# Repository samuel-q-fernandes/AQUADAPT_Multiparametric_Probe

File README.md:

# Development of a Cost-Effective Multiparametric Probe for Continuous, Real-Time Monitoring of Aquatic Environments

**AQUADAPT | AQUA-V1** is an open-source platform for in-situ water-quality/quantity monitoring (**pH, electrical conductivity (EC), temperature, and water level**). The system targets robust, long-term field deployments with an emphasis on reproducibility, traceability, and low total cost.

The hardware integrates an **ESP32** controller (LILYGO® T-Call with **SIM800L**) for data acquisition and processing, plus **GSM/GPRS** telemetry, **microSD** logging, and **solar power** support (MPPT + Li-ion). Firmware duty-cycles sensing and transmission, then enters **deep sleep** between cycles to minimize average power consumption, enabling multi-day autonomy and continuous operation under normal sunlight.

This repository provides the full stack: **KiCad** design files, **Arduino/C++** firmware, a **PHP API** for authenticated data ingest, the **SQL schema** to bootstrap the database, and a **web dashboard** for data visualization. Documentation includes wiring, configuration, deployment notes, and server setup.

To support transparent metrology, the docs also detail the complete measurement workflow and a **GUM-conforming uncertainty budget** (expanded uncertainties reported at *k* = 2), making results auditable across deployments. A link to the peer-reviewed manuscript will be added here upon acceptance.

Software is released under the **MIT License** (see `LICENSE`). 
**A link to the peer-reviewed manuscript will be added here upon acceptance by the journal.**

## Bill of Materials (BOM)

*A summarized BOM based on the components described in the manuscript. 

> **Target cost:** sub-€1,000 (sensor/probe choices and enclosure options drive most of the variation).

| Subsystem | Item / Model | Qty | Notes |
|---|---|---:|---|
| **MCU, comms & logging** | **LILYGO® TTGO T-Call v1.4** (ESP32 + SIM800L) | 1 | ESP32 controller with integrated GSM/GPRS modem; UART to modem, SPI to microSD. |
|  | **microSD module + 16 GB microSD card** | 1 | On-device redundant logging (CSV/JSON). |
| **Analog / digital interfaces** | **EZO™ Isolator / isolated carrier (pH)** | 1 | Electrical isolation to reduce ground/EMI coupling into pH front-end. |
|  | **EZO™ Conductivity (EC) Circuit** | 1 | Digital EC interface (I²C/UART); temperature aware as configured. |
|  | **MT3608 DC–DC boost converter** | 1 | Boost supply (e.g., 5 V → 12–36 V) for the level/pressure sensor. |
| **Sensors** | **Mini Lab-grade pH probe (ENV-20-pH)** | 1 | Glass electrode; used with Nernst temperature compensation. |
|  | **Mini Conductivity probe K = 1.0 (ENV-20-EC-K1.0)** | 1 | EC probe; three-point calibration via cell constant. |
|  | **DS18B20 temperature sensor** | 1 | 12-bit (0.0625 °C); OneWire; **4.7 kΩ** pull-up to Vcc. |
|  | **Industrial submersible pressure/level sensor (0–5 m)** | 1 | Analog output; hydrostatic level; powered via MT3608 boost. |
| **Custom PCB** | **Main carrier PCB (≈100 × 100 mm)** | 1 | Breakouts and headers for pH/EC/level/DS18B20, modem, power rails, and microSD. |
| **Power** | **PV panel (≈6 V / 5 W)** | 1 | Solar charging for autonomous operation. |
|  | **MPPT charge/power manager (≈900 mA charge)** | 1 | Manages PV → Li-ion charging and system power. |
|  | **Li-ion battery (3.7 V, ~4000 mAh)** | 1 | Energy storage; supports multi-day duty cycle. |
| **Cabling & enclosure** | **IP-rated enclosure with cable glands** | 1 | Houses electronics; strain relief and desiccant recommended. |
|  | **Sensor cable harness (~7 m)** | 2 | Extends probes from housing to water column. |
| **Passives** | **4.7 kΩ resistor** | 1 | DS18B20 pull-up. |
|  | **Sense resistor ~120 Ω (level channel)** | 1 | Per level/pressure readout design. |
| **Calibration materials** | **pH buffers (e.g., pH 4, 7, 9, 10; traceable)** | set | Used for multi-point pH calibration at measurement temperature. |
|  | **EC standards (e.g., 1413, 12 880, 80 000 µS/cm)** | set | Used to estimate cell constant and verify linearity. |

### Sourcing and integration notes
- **Region & connectivity:** confirm 2G/GPRS availability; if unavailable, substitute LTE-M/NB-IoT modem with matching firmware and power profile.  
- **Power budget:** size PV and battery for sampling + telemetry duty cycle and local insolation; include winter/cloud margins.  
- **EMI & grounding:** keep high-impedance pH paths short and away from digital lines; consider shielded cables and star-grounding.  
- **Calibration traceability:** document buffer/standard lot numbers, temperatures, and dates; store calibration IDs in firmware/config.

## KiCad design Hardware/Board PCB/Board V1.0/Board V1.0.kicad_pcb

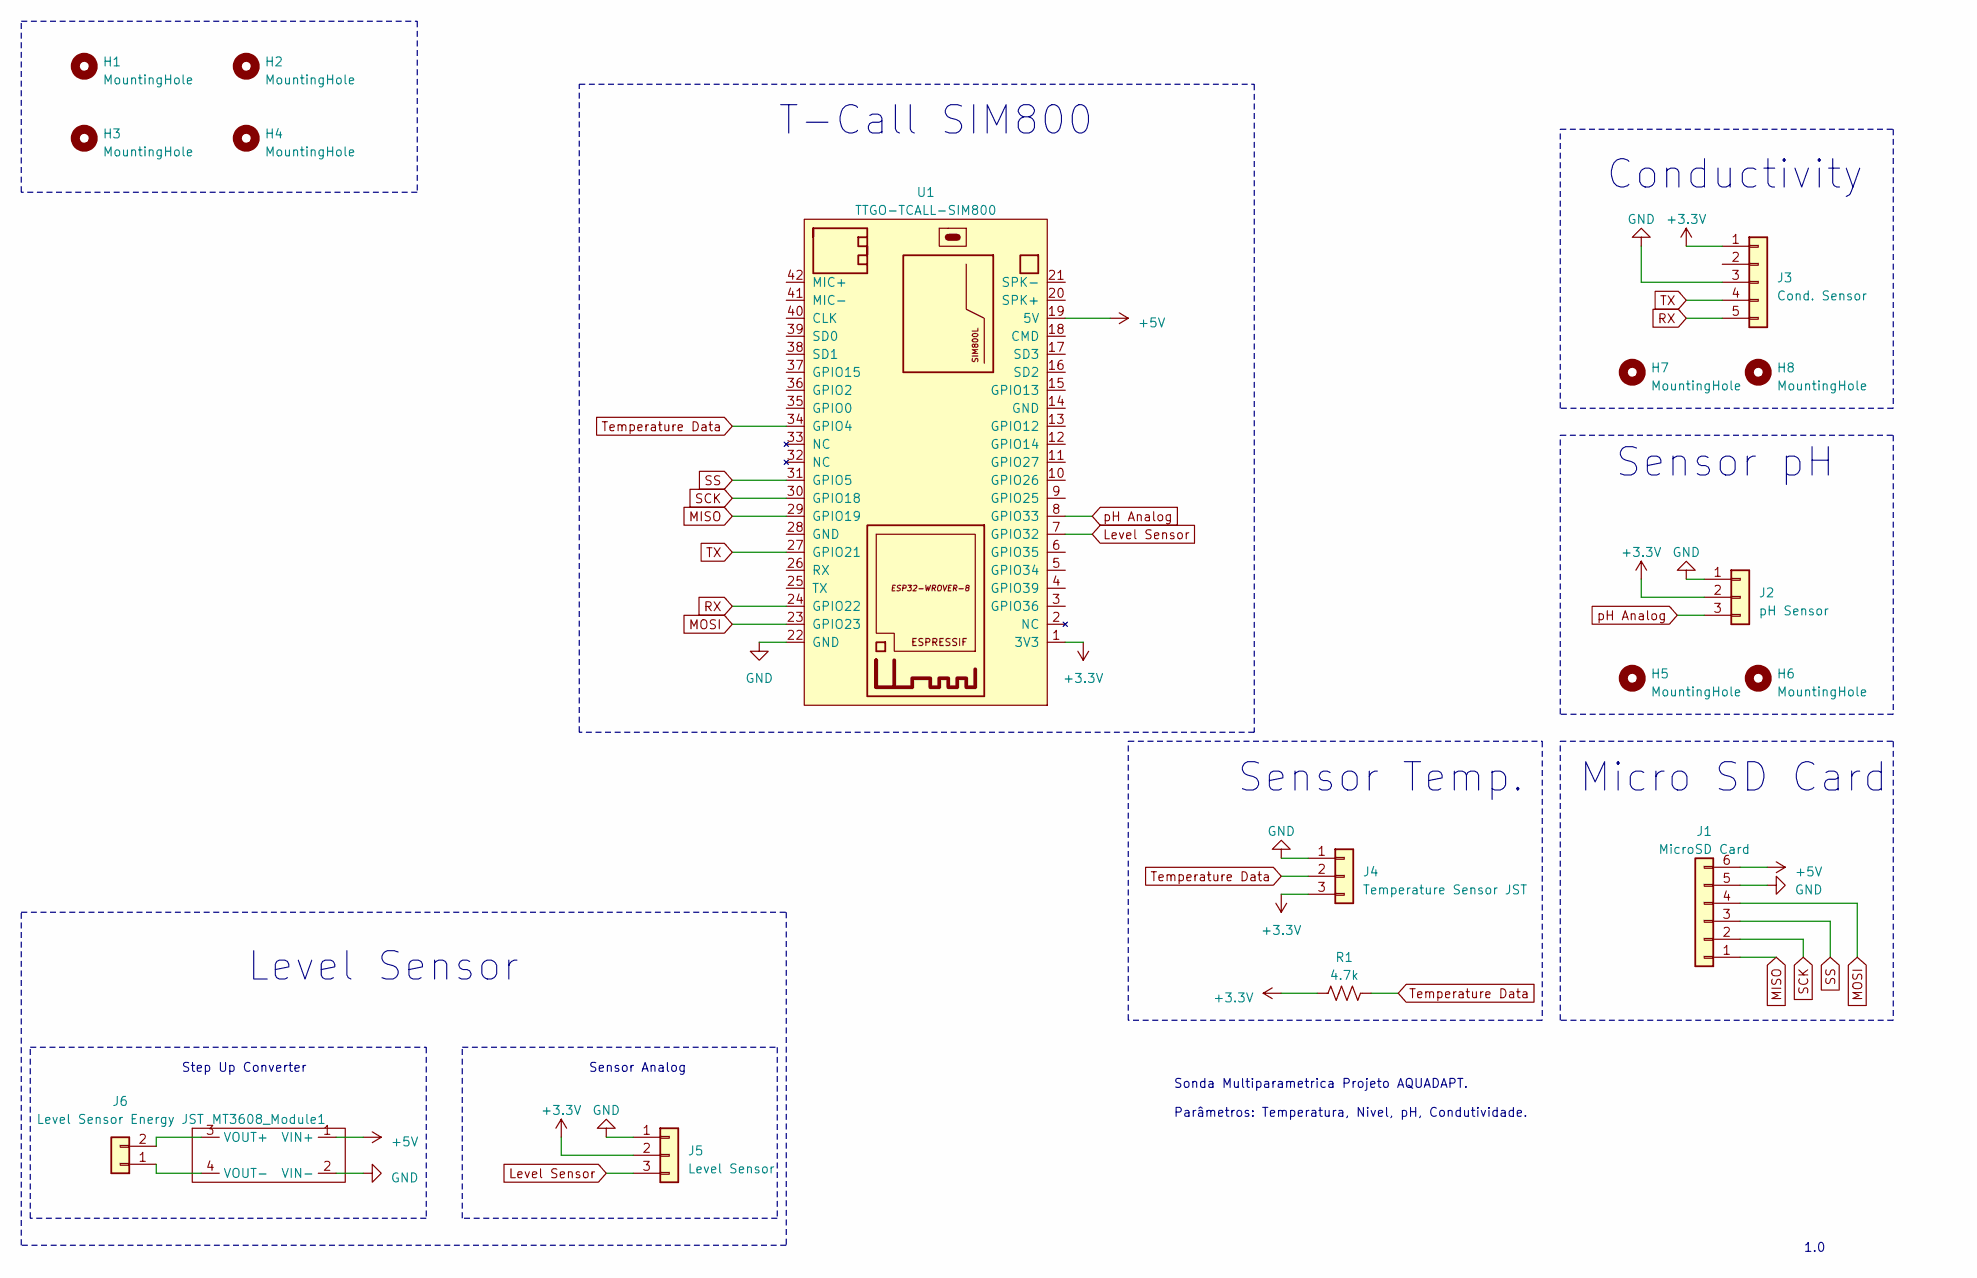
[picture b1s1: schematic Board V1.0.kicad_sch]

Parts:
H1, H2, H3, H4, H5, H6, H7, H8: MountingHole; MountingHole_3mm
J1: MicroSD Card; PinSocket_1x06_P2.54mm_Vertical
J2: pH Sensor; PinSocket_1x03_P2.54mm_Vertical
J3: Cond. Sensor; PinSocket_1x05_P2.54mm_Vertical
J4: Temperature Sensor JST; PinSocket_1x03_P2.54mm_Vertical
J5: Level Sensor; PinSocket_1x03_P2.54mm_Vertical
J6: Level Sensor Energy JST; PinSocket_1x02_P2.54mm_Vertical
MT3608_Module1: MT3608-Module
R1: 4.7k; R_Axial_DIN0207_L6.3mm_D2.5mm_P10.16mm_Horizontal
U1: TTGO-TCALL-SIM800

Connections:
+3.3V: J2.2, J3.1, J4.3, J5.2, R1.1, U1.1 (3V3)
+5V: J1.6, MT3608_Module1.1 (VIN+), U1.19 (5V)
GND: J1.5, J2.1, J3.3, J4.1, J5.1, MT3608_Module1.2 (VIN-), U1.22 (GND)
Level Sensor: J5.3, U1.7 (GPIO32)
MISO: J1.1, U1.29 (GPIO19)
MOSI: J1.4, U1.23 (GPIO23)
unnamed: J6.1, MT3608_Module1.4 (VOUT-)
unnamed: J6.2, MT3608_Module1.3 (VOUT+)
RX: J3.5, U1.24 (GPIO22)
SCK: J1.2, U1.30 (GPIO18)
SS: J1.3, U1.31 (GPIO5)
TX: J3.4, U1.27 (GPIO21)
Temperature Data: J4.2, R1.2, U1.34 (GPIO4)
pH Analog: J2.3, U1.8 (GPIO33)

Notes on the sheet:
Sensor Temp.
Step Up Converter
Conductivity
Sonda Multiparametrica Projeto AQUADAPT. Parâmetros: Temperatura, Nivel, pH, Condutividade.
T-Call SIM800
Sensor Analog
1.0
Sensor pH
Level Sensor
Micro SD Card

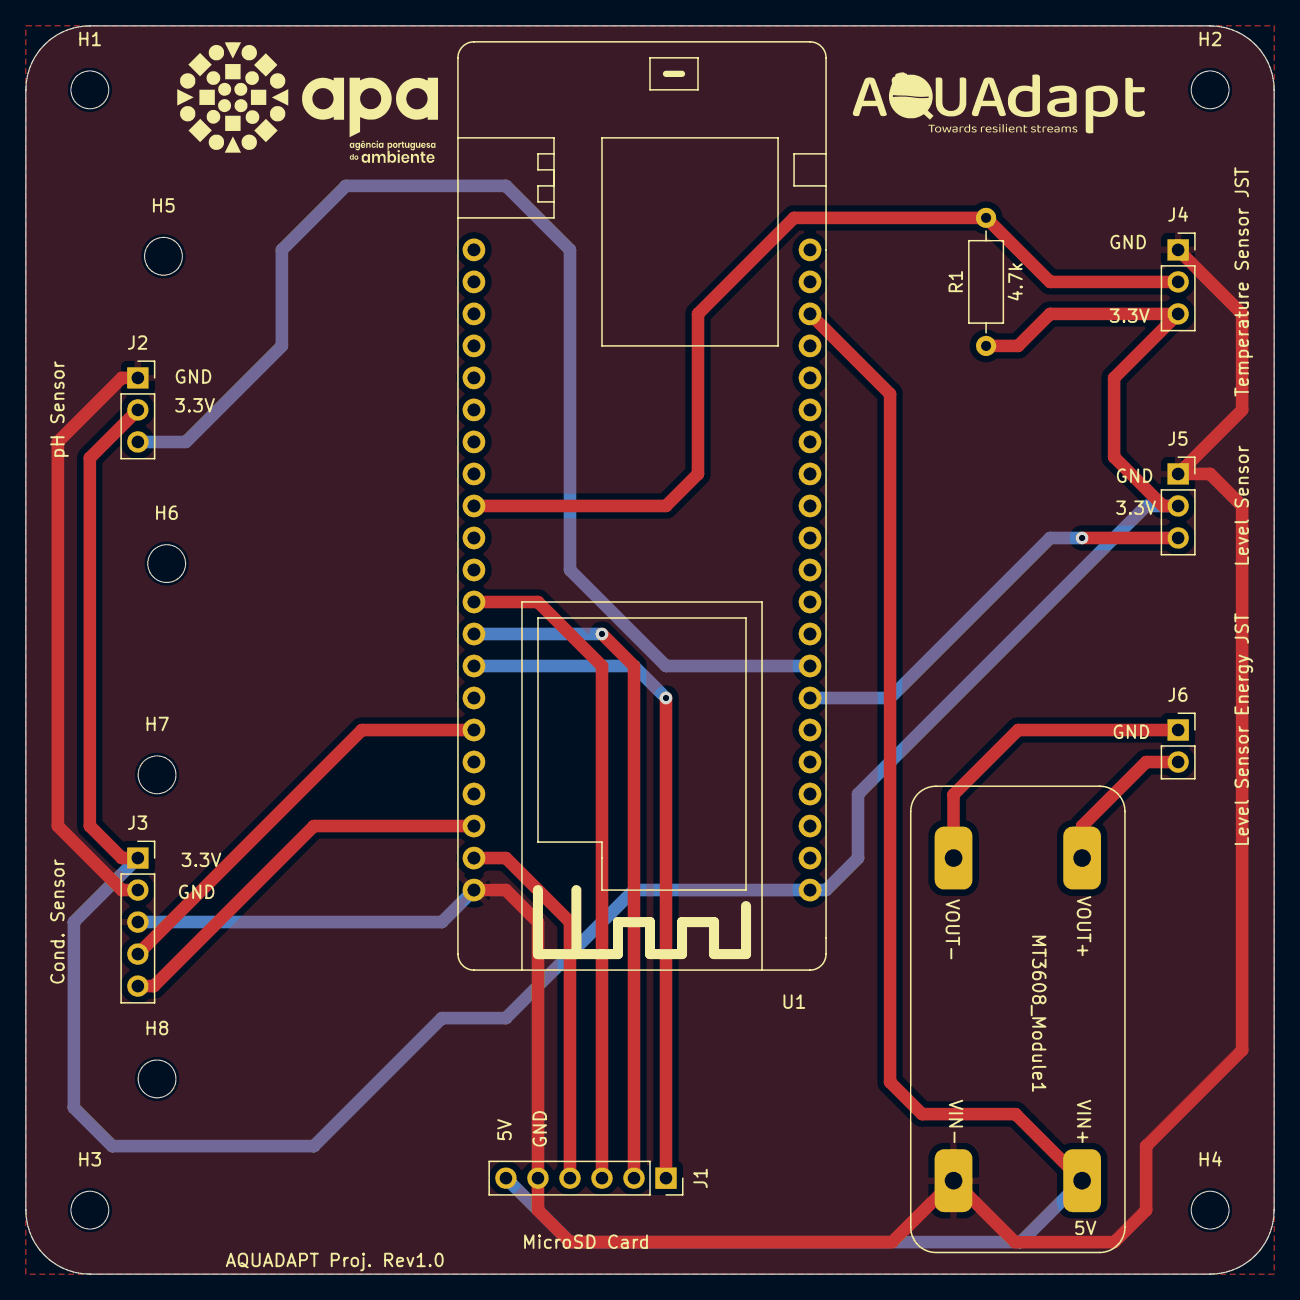
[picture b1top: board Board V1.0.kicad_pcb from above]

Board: 2 copper layers, 99.1 x 99.1 mm, 17 parts (0 on the bottom side), 14 nets.

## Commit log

2025-11-03 Documentation
    Images
2025-11-03 Folders
    Introducing new folders for the project
2025-11-03 Board PCB
    Introducing Board PCB
2025-11-03 Software
    Introducing Dashboard
2025-11-03 ESP-32 Code
    Introduction of the multiparameter probe ESP32 - code
2025-11-03 introducing new images
2025-11-03 New Names Images
2025-11-03 Introducing Server information
2025-11-04 Documentation
